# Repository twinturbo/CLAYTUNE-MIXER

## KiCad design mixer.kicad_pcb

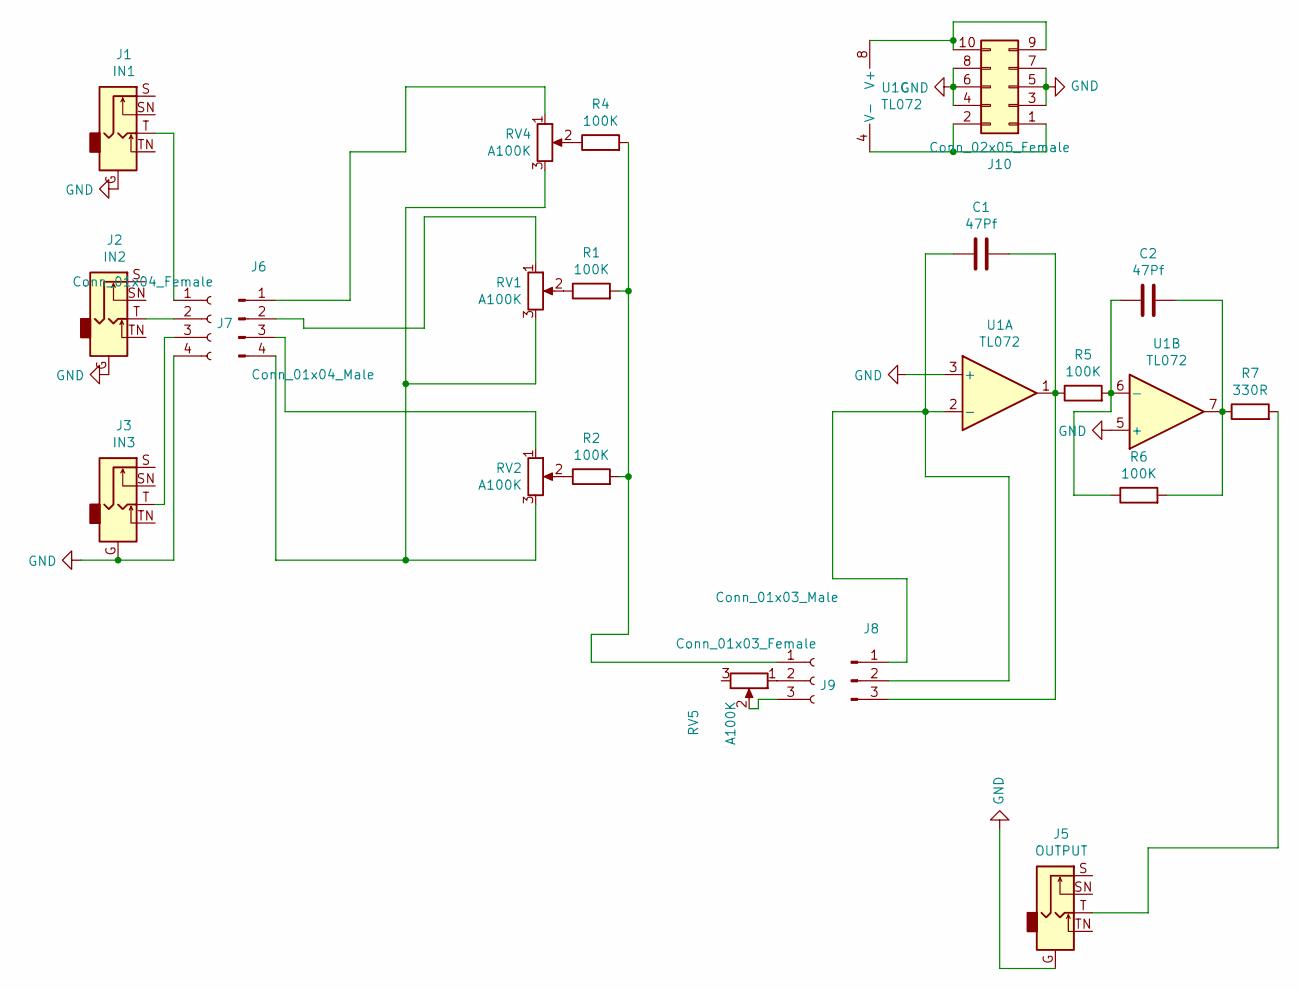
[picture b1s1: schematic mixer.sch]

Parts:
C1, C2: 47Pf; C_Disc_D7.5mm_W5.0mm_P10.00mm
J1: IN1; Jack_6.5mmLMNC
J2: IN2; Jack_6.5mmLMNC
J3: IN3; Jack_6.5mmLMNC
J5: OUTPUT; Jack_6.5mmLMNC
J6: Conn_01x04_Male; PinHeader_1x04_P2.54mm_Vertical
J7: Conn_01x04_Female; PinSocket_1x04_P2.54mm_Vertical
J8: Conn_01x03_Male; PinHeader_1x03_P2.54mm_Vertical
J9: Conn_01x03_Female; PinSocket_1x03_P2.54mm_Vertical
J10: Conn_02x05_Female; IDC-Header_2x05_P2.54mm_Vertical
R1, R2, R4, R5, R6: 100K; R_Axial_DIN0207_L6.3mm_D2.5mm_P10.16mm_Horizontal
R7: 330R; R_Axial_DIN0207_L6.3mm_D2.5mm_P10.16mm_Horizontal
RV1, RV2, RV4, RV5: A100K; Potentiometer_Alps_RK09K_Single_Vertical
U1: TL072; DIP-8_W7.62mm

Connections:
GND: J1.G, J2.G, J3.G, J5.G, J7.4, J10.3, J10.4, J10.5, J10.6, J10.7, J10.8, U1.3 (+), U1.5 (+)
unnamed: C1.1, J8.1, J8.2, U1.2 (-)
unnamed: C1.2, J8.3, R5.1, U1.1
unnamed: C2.1, R5.2, R6.1, U1.6 (-)
unnamed: C2.2, R6.2, R7.1, U1.7
unnamed: J1.T, J7.1
unnamed: J2.T, J7.2
unnamed: J3.T, J7.3
unnamed: J5.T, R7.2
unnamed: J6.1, RV4.1
unnamed: J6.2, RV1.1
unnamed: J6.3, RV2.1
unnamed: J6.4, RV1.3, RV2.3, RV4.3
unnamed: J9.1, R1.2, R2.2, R4.2
unnamed: J9.2, RV5.1
unnamed: J9.3, RV5.2
unnamed: J10.1, J10.2, U1.4 (V-)
unnamed: J10.9, J10.10, U1.8 (V+)
unnamed: R1.1, RV1.2
unnamed: R2.1, RV2.2
unnamed: R4.1, RV4.2

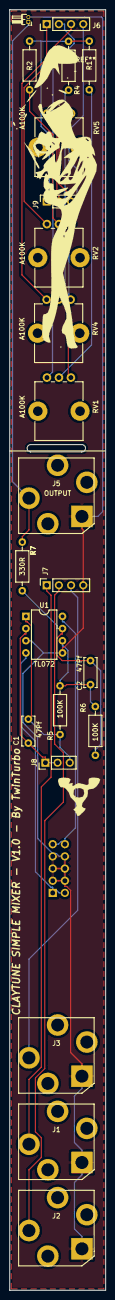
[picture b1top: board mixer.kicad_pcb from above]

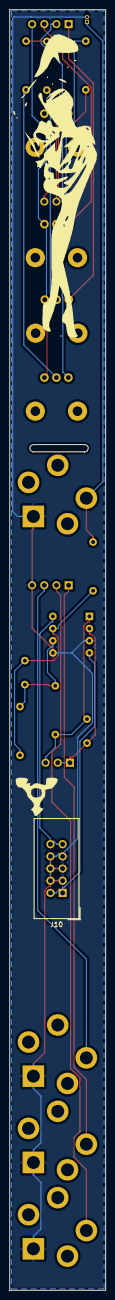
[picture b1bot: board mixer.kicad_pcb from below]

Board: 2 copper layers, 20.0 x 267.0 mm, 26 parts (2 on the bottom side), 21 nets.

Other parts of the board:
G1: LOGO; shoebw-cu
G2, G3: LOGO; t2
GIJO: LOGO; Girl7

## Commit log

2020-12-04 init
2020-12-05 autosync
2020-12-05 Tidy PCB/Panel Dirs
2020-12-05 Tidy PCB/Panel Dirs 2
2020-12-05 Tidy PCB/Panel Dirs 3
